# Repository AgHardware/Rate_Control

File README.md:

### [Nano RC12-2](Nano/RC12-2)
- uses a Nano (with ENC28J60 Ethernet shield) & an on-board mounted Cytron for rate control
	- either (1) [MD13S](https://www.cytron.io/p-13amp-6v-30v-dc-motor-driver) for single rate control
 	- or (1) [MD10C](https://www.cytron.io/c-motor-and-motor-driver/c-motor-driver/p-10amp-5v-30v-dc-motor-driver) for single rate control
- self assembled through-hole board, least expensive
- controls one rate
- can be connected to a relay module with another small pcb
- [OSHPARK](https://oshpark.com/shared_projects/UU8e90h9)

#
### [Teensy 4.1 RC11](Teensy/RC11_PCB)
- uses a Teensy & an on-board mounted Cytron for rate control
	- either (1) [MD13S](https://www.cytron.io/p-13amp-6v-30v-dc-motor-driver) for single rate control
 	- or (1) [MDD10A](https://www.cytron.io/p-10amp-5v-30v-dc-motor-driver-2-channels) for dual rate control
- small components are surface mount parts
- Teensy Ethernet or ESP8266 (ESP-12F) Wifi
- can control two rates and eight sections
	- 8 relays (SPST 12V output)
	- (2) 5V analog (pressure) inputs
	- (2) optically isolated digital (rate/pulse) inputs (5V)
- 5V Serial TTL header
- 3.3V I2C headers
	- supports optional external RelayDriver5 I2C board

#
### [ESP32 RC15](ESP32/RC15)
- uses an ESP32 (optional W5500 Ethernet Module)
- mostly surface mount parts
- can control two rates and 7-14 sections
	- (2) DRV8870 motor drivers with reversible outputs for rates
	- (7) DRV8870 motor drivers for either 7 reversible (motorized ball valve) outputs or 14 single ended (high or low) section outputs
- (4) 5V analog inputs (or 2 differential inputs)
- (2) optically isolated digital (rate/pulse) inputs, up to 12V
- RS485 chip & header
- 3.3V I2C header
	- supports optional external RelayDriver5 I2C board

#
### [RelayDriver5](RelayDriver5)
- PCA9535 based I2C IO expander
- designed to plug into 8 or 16 channel relay board with Qwiic cable

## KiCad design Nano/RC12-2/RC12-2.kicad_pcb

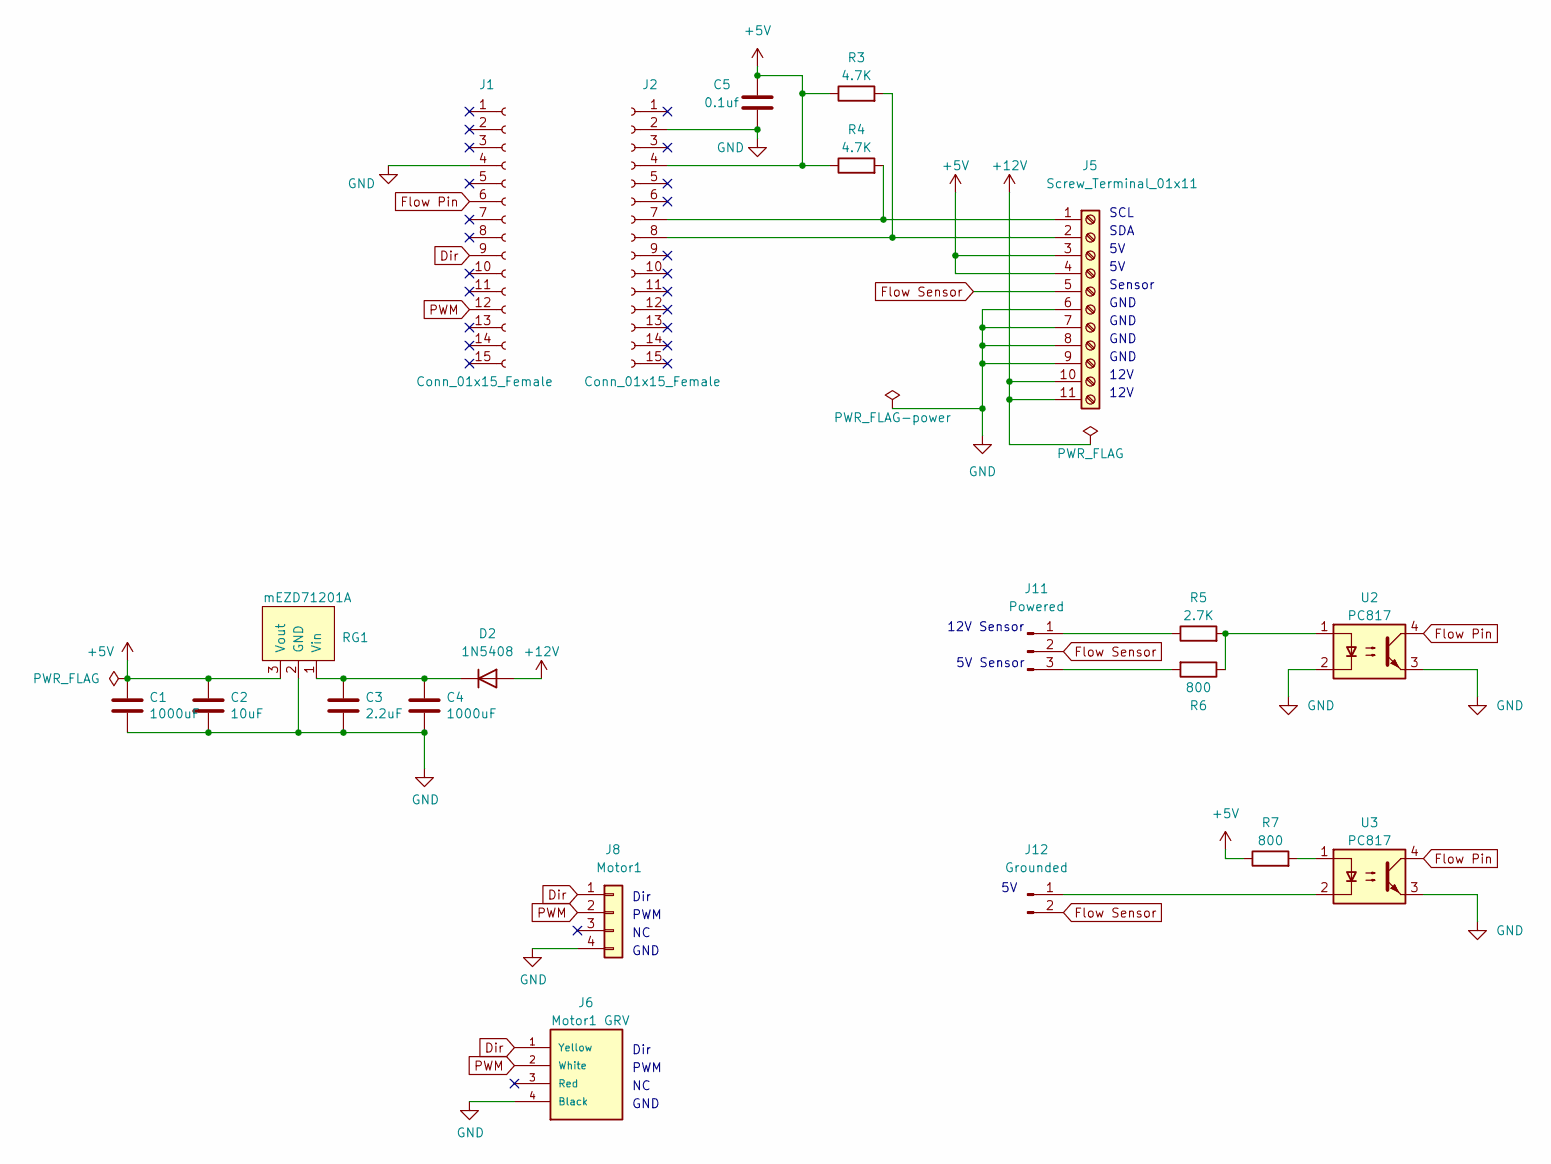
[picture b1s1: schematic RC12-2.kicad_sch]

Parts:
C1, C4: 1000uF; CP_Radial_D10.0mm_P5.00mm
C2: 10uF; C_Disc_D5.0mm_W2.5mm_P2.50mm
C3: 2.2uF; C_Disc_D5.0mm_W2.5mm_P2.50mm
C5: 0.1uf; C_Disc_D5.0mm_W2.5mm_P2.50mm
D2: 1N5408
J1, J2: Conn_01x15_Female; PinSocket_1x15_P2.54mm_Vertical
J5: Screw_Terminal_01x11; TerminalBlock_Phoenix_MKDS-1,5-11_1x11_P5.00mm_Horizontal
J6: Motor1 GRV; Grove
J8: Motor1; Molex_KK-254_AE-6410-04A_1x04_P2.54mm_Vertical
J11: Powered; PinHeader_1x03_P2.54mm_Vertical
J12: Grounded; PinHeader_1x02_P2.54mm_Vertical
R3, R4: 4.7K; R_Axial_DIN0207_L6.3mm_D2.5mm_P10.16mm_Horizontal
R5: 2.7K; R_Axial_DIN0207_L6.3mm_D2.5mm_P10.16mm_Horizontal
R6, R7: 800; R_Axial_DIN0207_L6.3mm_D2.5mm_P10.16mm_Horizontal
RG1: mEZD71201A
U2, U3: PC817

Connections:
+5V: C1.1, C2.1, C5.2, J2.4, J5.3, J5.4, R3.1, R4.1, R7.1, RG1.3 (Vout)
+12V: D2.2 (A), J5.10, J5.11
Dir: J1.9, J6.1 (Yellow), J8.1
Flow Pin: J1.6, U2.4, U3.4
Flow Sensor: J5.5, J11.2, J12.2
GND: C1.2, C2.2, C3.2, C4.2, C5.1, J1.4, J2.2, J5.6, J5.7, J5.8, J5.9, J6.4 (Black), J8.4, RG1.2 (GND), U2.2, U2.3, U3.3
unnamed: C3.1, C4.1, D2.1 (K), RG1.1 (Vin)
unnamed: J2.7, J5.1, R4.2
unnamed: J2.8, J5.2, R3.2
unnamed: J11.1, R5.1
unnamed: J11.3, R6.2
unnamed: J12.1, U3.2
unnamed: R5.2, R6.1, U2.1
unnamed: R7.2, U3.1
PWM: J1.12, J6.2 (White), J8.2

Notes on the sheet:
SCL
GND
SDA
5V Sensor
Dir
12V
12V Sensor
PWM
Sensor

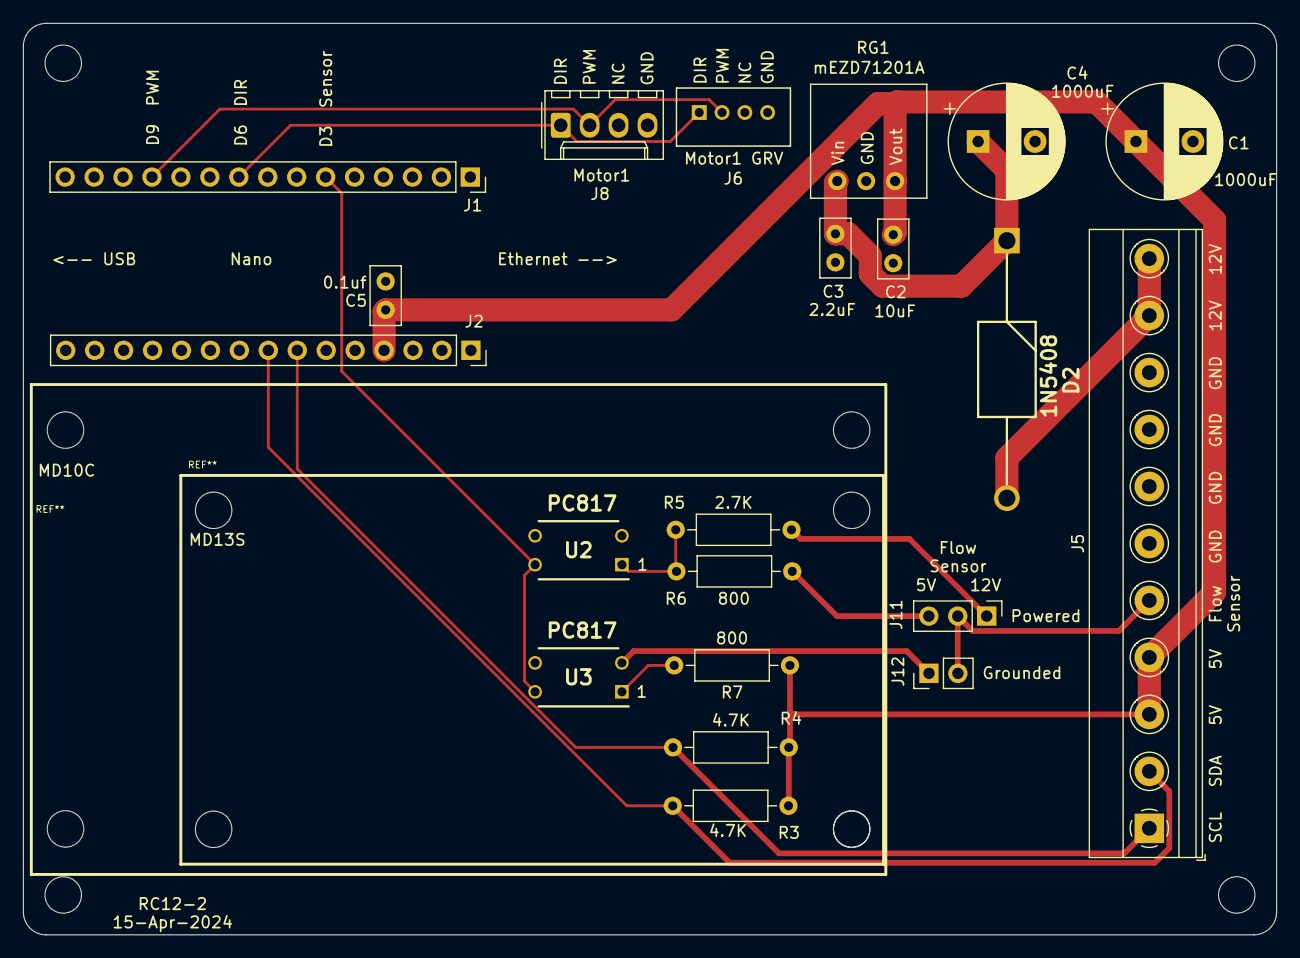
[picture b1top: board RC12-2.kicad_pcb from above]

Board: 2 copper layers, 110.0 x 80.0 mm, 25 parts (0 on the bottom side), 15 nets.

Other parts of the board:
 : MountingHole_3.2mm_M3
 #2,  #3,  #4: MountingHole_3.2mm_M3

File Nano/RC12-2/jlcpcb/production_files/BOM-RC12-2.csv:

Comment,Designator,Footprint,LCSC
2.7K,"R5,R6,R7",R_Axial_DIN0207_L6.3mm_D2.5mm_P10.16mm_Horizontal,C119333
4.7K,"R3,R4",R_Axial_DIN0207_L6.3mm_D2.5mm_P10.16mm_Horizontal,C119339
10uF,C2,C_Disc_D5.0mm_W2.5mm_P2.50mm,C2761733
Screw_Terminal_01x11,J5,"TerminalBlock_Phoenix_MKDS-1,5-11_1x11_P5.00mm_Horizontal",C2802625
Conn_01x15_Female,"J1,J2",PinSocket_1x15_P2.54mm_Vertical,C2932676
PC817,"U2,U3",PC817,C390734
Motor1 GRV,J6,Grove,C403774
Grounded,J12,PinHeader_1x02_P2.54mm_Vertical,C492401
Powered,J11,PinHeader_1x03_P2.54mm_Vertical,C49257
1000uF,"C1,C4",CP_Radial_D10.0mm_P5.00mm,C503217
2.2uF,C3,C_Disc_D5.0mm_W2.5mm_P2.50mm,C5181476
0.1uf,C5,C_Disc_D5.0mm_W2.5mm_P2.50mm,C5632430
1N5408,D2,1N5408,C698639
Motor1,J8,Molex_KK-254_AE-6410-04A_1x04_P2.54mm_Vertical,C86504
mEZD71201A,RG1,mEZD71201A,

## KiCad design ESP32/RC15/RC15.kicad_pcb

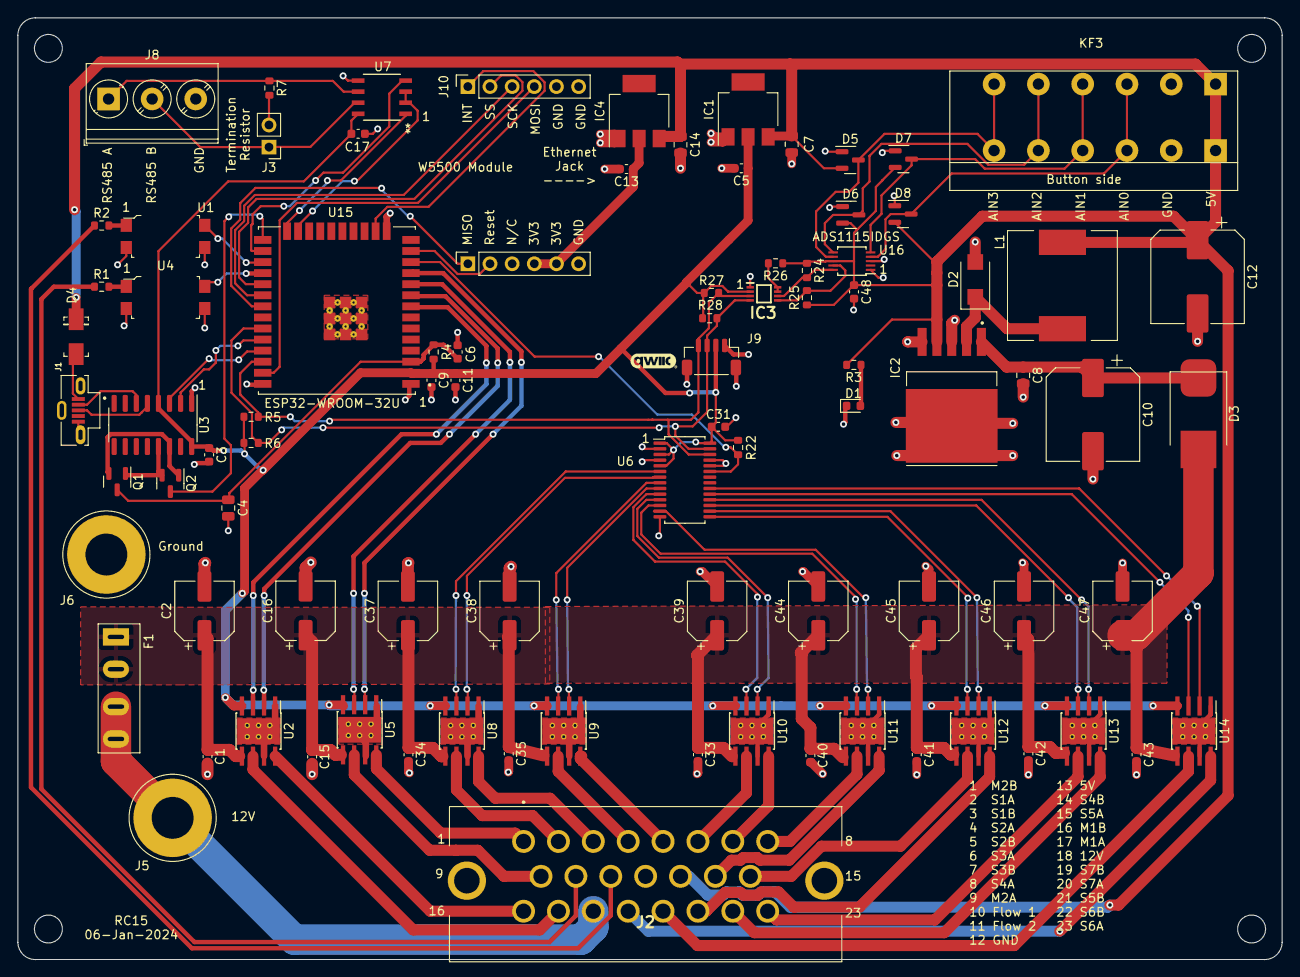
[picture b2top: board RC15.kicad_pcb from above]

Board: 2 copper layers, 145.0 x 108.0 mm, 92 parts (0 on the bottom side), 82 nets.

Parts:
 : MountingHole_3.2mm_M3
 #2,  #3,  #4: MountingHole_3.2mm_M3
C1, C3, C6, C9, C15, C17, C31, C33, C34, C35, C40, C41, C42, C43, C48: 0.1uF; C_0603_1608Metric
C2, C16, C37, C38, C39, C44, C45, C46, C47: 47uF; CP_Elec_6.3x5.4
C4, C8: 1uF; C_0805_2012Metric
C5, C11, C13: 22uF; C_0603_1608Metric
C7, C14: 10uF; C_0805_2012Metric
C10: 470uF; CP_Elec_10x10.5
C12: 330uF; CP_Elec_10x10.5
D1: LED; LED_0603_1608Metric
D2: SS36; SMA(DO-214AC)
D3: S10MC; D_SMC_larger_pads
D4: M7 - C95872; DO-214AC
D5, D6, D7, D8: BAV99; SOT-23
F1: C492610; Fuse_Holder_C492610
IC1, IC4: AZ1117; SOT-223
IC2: XL2596; TO263-5L
IC3: PCA9306DCUR
J1: 105133-0011; MOLEX_105133-0011
J2: 776087-1-776087-1; 7760871
J3: Conn_01x02_Pin; PinHeader_1x02_P2.54mm_Vertical
J5: 12V; PowerPin
J6: Ground; PowerPin
J7, J10: Conn_01x06_Socket; PinSocket_1x06_P2.54mm_Vertical
J8: Screw_Terminal_01x03; TerminalBlock_Phoenix_PT-1,5-3-5.0-H_1x03_P5.00mm_Horizontal
J9: I2C; Qwic_vertical
KF3: KF142V-5.0-6P; KF142V-5.08-6P
L1: SMDRI127-330MT; TMPA1265SP-101MN-D
Q1, Q2: BSS138; SOT-23
R1, R2: 2.7K; R_0603_1608Metric
R3: 500; R_0603_1608Metric
R4, R22: 10K; R_0603_1608Metric
R5, R6: 2.2K; R_0603_1608Metric
R7: 120; R_0603_1608Metric
R24, R25: 341; R_0603_1608Metric
R26: 200K; R_0603_1608Metric
R27, R28: 217; R_0603_1608Metric
U1, U4: PC817 chip; SMD-4_4.6x7.62mm_P2.54mm
U2, U5, U8, U9, U10, U11, U12, U13, U14: DRV8870DDA; Texas_HTSOP-8-1EP_3.9x4.9mm_P1.27mm_EP2.95x4.9mm_Mask2.4x3.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
U3: CH340C; SOIC-16_3.9x9.9mm_P1.27mm
U6: PCA9685PW; TSSOP-28_4.4x9.7mm_P0.65mm
U7: C9943; 21-0041B_8_MXM
U15: ESP32-WROOM-32U; XCVR_ESP32-WROOM-32U
U16: ADS1115IDGS; TSSOP-10_3x3mm_P0.5mm

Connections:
+3.3V: C3.1, C5.1, C9.1, C11.1, C17.1, C31.1, IC1.2 (OUTPUT), IC3.2 (VREF1), J9.2, R4.1, R5.1, R6.1, R22.1, R27.1, R28.1, U2.4 (VREF), U3.4 (V3), U3.16 (VCC), U5.4 (VREF), U6.1 (A0), U6.3 (A2), U6.5 (A4), U6.28 (VDD), U7.8 (VCC), U8.4 (VREF), U9.4 (VREF), U10.4 (VREF), U11.4 (VREF), U12.4 (VREF), U13.4 (VREF), U14.4 (VREF), U15.2 (3V3)
+5V: C7.1, C12.1, C14.1, C48.1, D4.1 (K), D5.2 (A), D6.2 (A), D7.2 (A), D8.2 (A), IC1.3 (INPUT), IC2.4 (Feedback), IC4.3 (INPUT), J2.13, KF3.1, L1.2, R3.2, R24.1, R25.1, R26.1, U16.8 (VDD)
+12V: C1.1, C2.1, C15.1, C16.1, C33.1, C34.1, C35.1, C37.1, C38.1, C39.1, C40.1, C41.1, C42.1, C43.1, C44.1, C45.1, C46.1, C47.1, D3.2 (A), F1.1, U2.5 (VM), U5.5 (VM), U8.5 (VM), U9.5 (VM), U10.5 (VM), U11.5 (VM), U12.5 (VM), U13.5 (VM), U14.5 (VM)
FlowPin1: U4.4, U15.28 (IO17)
FlowPin2: U1.4, U15.27 (IO16)
FlowSensor1: J2.10, R1.1
FlowSensor2: J2.11, R2.1
GND: C1.2, C2.2, C3.2, C4.2, C5.2, C6.2, C7.2, C8.2, C9.2, C10.2, C11.2, C12.2, C13.2, C14.2, C15.2, C16.2, C17.2, C31.2, C33.2, C34.2, C35.2, C37.2, C38.2, C39.2, C40.2, C41.2, C42.2, C43.2, C44.2, C45.2, C46.2, C47.2, C48.2, D1.1 (K), D2.2, D5.1 (K), D6.1 (K), D7.1 (K), D8.1 (K), IC1.1 (ADJ/GND), IC2.3 (GND), IC2.5 (On/Off), IC2.6 (GND_1), IC3.1 (GND), IC4.1 (ADJ/GND), J1.5 (GND), J1.S1 (SHIELD), J1.S2 (SHIELD), J1.S3 (SHIELD), J2.12, J6.1, J7.6, J8.3, J9.1, J9.MP (MountPin), J10.5, J10.6, KF3.2, U1.2, U1.3, U2.1 (GND), U2.7 (ISEN), U2.9 (GND), U3.1 (GND), U4.2, U4.3, U5.1 (GND), U5.7 (ISEN), U5.9 (GND), U6.2 (A1), U6.4 (A3), U6.14 (VSS), U6.24 (A5), U6.25 (EXTCLK), U7.5 (GND), U8.1 (GND), U8.7 (ISEN), U8.9 (GND), U9.1 (GND), U9.7 (ISEN), U9.9 (GND), U10.1 (GND), U10.7 (ISEN), U10.9 (GND), U11.1 (GND), U11.7 (ISEN), U11.9 (GND), U12.1 (GND), U12.7 (ISEN), U12.9 (GND), U13.1 (GND), U13.7 (ISEN), U13.9 (GND), U14.1 (GND), U14.7 (ISEN), U14.9 (GND), U15.1 (GND), U15.15 (GND), U15.38 (GND), U15.G.1 (GND), U15.G.2 (GND), U15.G.4 (GND), U15.G.5 (GND), U15.G.6 (GND), U15.G.7 (GND), U15.G.8 (GND), U15.G.9 (GND), U15.G.10 (GND), U15.G.11 (GND), U15.G.12 (GND), U15.G.13 (GND), U15.G.14 (GND), U15.G.15 (GND), U15.G.16 (GND), U15.G.17 (GND), U15.G.18 (GND), U15.G.19 (GND), U15.G.20 (GND), U15.G.21 (GND), U15.G.22 (GND), U16.1 (ADDR), U16.3 (GND)
INTn: J10.1, U15.16 (IO13)
M1A: J2.17, U2.6 (OUT1)
M1B: J2.16, U2.8 (OUT2)
M1_IN1: U2.3 (IN1), U15.8 (I032)
M1_IN2: U2.2 (IN2), U15.9 (I033)
M2A: J2.9, U5.6 (OUT1)
M2B: J2.1, U5.8 (OUT2)
M2_IN1: U5.3 (IN1), U15.10 (I025)
M2_IN2: U5.2 (IN2), U15.11 (I026)
MISO: J7.1, U15.31 (IO19)
MOSI: J10.4, U15.37 (IO23)
unnamed: D1.2 (A), R3.1
unnamed: C8.1, C10.1, D3.1 (K), IC2.1 (VIN)
unnamed: D4.2 (A), J1.1 (VBUS)
unnamed: D2.1, IC2.2 (Output), L1.1
unnamed: IC3.7 (VREF2), IC3.8 (EN), R26.2
unnamed: IC3.6 (SCL2), R24.2, U16.10 (SCL)
unnamed: IC3.5 (SDA2), R25.2, U16.9 (SDA)
unnamed: C13.1, IC4.2 (OUTPUT), J7.4, J7.5
unnamed: J1.3 (D+), U3.5 (UD+)
unnamed: J1.2 (D-), U3.6 (UD-)
unnamed: J3.1, J8.2, U7.7 (B)
unnamed: J3.2, R7.2
unnamed: F1.2, J2.18, J5.1
unnamed: J8.1, R7.1, U7.6 (A)
unnamed: Q1.1 (G), Q2.2 (S), U3.13 (~DTR)
unnamed: Q1.2 (S), Q2.1 (G), U3.14 (~RTS)
unnamed: Q2.3 (D), U15.25 (IO0)
unnamed: R1.2, U4.1
unnamed: R2.2, U1.1
unnamed: U6.6 (LED0), U8.3 (IN1)
unnamed: U6.7 (LED1), U8.2 (IN2)
unnamed: U6.8 (LED2), U9.3 (IN1)
unnamed: U6.9 (LED3), U9.2 (IN2)
unnamed: U6.10 (LED4), U10.3 (IN1)
unnamed: U6.11 (LED5), U10.2 (IN2)
unnamed: U6.12 (LED6), U11.3 (IN1)
unnamed: U6.13 (LED7), U11.2 (IN2)
unnamed: U6.15 (LED8), U12.3 (IN1)
unnamed: U6.16 (LED9), U12.2 (IN2)
unnamed: U6.17 (LED10), U13.3 (IN1)
unnamed: U6.18 (LED11), U13.2 (IN2)
unnamed: U6.19 (LED12), U14.3 (IN1)
unnamed: U6.20 (LED13), U14.2 (IN2)
unnamed: D8.3 (K), KF3.3, U16.4 (AIN0)
unnamed: D7.3 (K), KF3.4, U16.5 (AIN1)
unnamed: D6.3 (K), KF3.5, U16.6 (AIN2)
unnamed: D5.3 (K), KF3.6, U16.7 (AIN3)
OutputEnable: R22.2, U6.23 (~OE), U15.12 (IO27)
RS485_Enable: U7.2 (~RE), U7.3 (DE), U15.23 (IO15)
RX2: U7.1 (RO), U15.24 (IO2)
ResetNW: J7.2, U15.13 (IO14)
S1A: J2.2, U8.6 (OUT1)
S1B: J2.3, U8.8 (OUT2)
S2A: J2.4, U9.6 (OUT1)
S2B: J2.5, U9.8 (OUT2)
S3A: J2.6, U10.6 (OUT1)
S3B: J2.7, U10.8 (OUT2)
S4A: J2.8, U11.6 (OUT1)
S4B: J2.14, U11.8 (OUT2)
S5A: J2.15, U12.6 (OUT1)
S5B: J2.21, U12.8 (OUT2)
S6A: J2.23, U13.6 (OUT1)
S6B: J2.22, U13.8 (OUT2)
S7A: J2.20, U14.6 (OUT1)
S7B: J2.19, U14.8 (OUT2)
SCK: J10.3, U15.30 (IO18)
SCL: IC3.3 (SCL1), J9.4, R5.2, R27.2, U6.26 (SCL), U15.36 (IO22)
SDA: IC3.4 (SDA1), J9.3, R6.2, R28.2, U6.27 (SDA), U15.33 (IO21)
SS: J10.2, U15.29 (IO5)
TX2: U7.4 (DI), U15.26 (IO4)
uC_EN: C4.1, C6.1, Q1.3 (D), R4.2, U15.3 (EN)
uC_RX: U3.2 (TXD), U15.34 (RXD0)
uC_TX: U3.3 (RXD), U15.35 (TXD0)

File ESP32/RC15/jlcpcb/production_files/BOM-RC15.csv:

Comment,Designator,Footprint,LCSC
200K,R26,R_0603_1608Metric,C105574
2.7K,"R1,R2",R_0603_1608Metric,C13167
0.1uF,"C1,C15,C17,C3,C31,C33,C34,C35,C40,C41,C42,C43,C48,C6,C9",C_0603_1608Metric,C14663
10uF,"C14,C7",C_0805_2012Metric,C15850
I2C,J9,Qwic_vertical,C160390
S10MC,D3,D_SMC_larger_pads,C169472
120,R7,R_0603_1608Metric,C22787
500,R3,R_0603_1608Metric,C22808
341,"R24,R25",R_0603_1608Metric,C23138
BAV99,"D5,D6,D7,D8",SOT-23,C2500
BSS138,"Q1,Q2",SOT-23,C255592
10K,"R22,R4",R_0603_1608Metric,C25804
217,"R27,R28",R_0603_1608Metric,C25811
PCA9685PW,U6,TSSOP-28_4.4x9.7mm_P0.65mm,C2678753
1uF,"C4,C8",C_0805_2012Metric,C28323
47uF,"C16,C2,C37,C38,C39,C44,C45,C46,C47",CP_Elec_6.3x5.4,C2836440
SS36,D2,SMA(DO-214AC),C2903825
330uF,C12,CP_Elec_10x10.5,C3032175
470uF,C10,CP_Elec_10x10.5,C310845
PCA9306DCUR,IC3,PCA9306DCUR,C33196
ADS1115IDGS,U16,TSSOP-10_3x3mm_P0.5mm,C37593
776087-1-776087-1,J2,7760871,C378893
Conn_01x06_Socket,"J10,J7",PinSocket_1x06_P2.54mm_Vertical,C40877
2.2K,"R5,R6",R_0603_1608Metric,C4190
KF142V-5.0-6P,KF3,KF142V-5.08-6P,C475138
C492610,F1,Fuse_Holder_C492610,C492610
Screw_Terminal_01x03,J8,"TerminalBlock_Phoenix_PT-1,5-3-5.0-H_1x03_P5.00mm_Horizontal",C5188441
105133-0011,J1,MOLEX_105133-0011,C586226
22uF,"C11,C13,C5",C_0603_1608Metric,C59461
PC817 chip,"U1,U4",SMD-4_4.6x7.62mm_P2.54mm,C66405
ESP32-WROOM-32U,U15,XCVR_ESP32-WROOM-32U,C701344
XL2596,IC2,TO263-5L,C74190
Conn_01x02_Pin,J3,PinHeader_1x02_P2.54mm_Vertical,C7494857
LED,D1,LED_0603_1608Metric,C84263
CH340C,U3,SOIC-16_3.9x9.9mm_P1.27mm,C84681
DRV8870DDA,"U10,U11,U12,U13,U14,U2,U5,U8,U9",Texas_HTSOP-8-1EP_3.9x4.9mm_P1.27mm_EP2.95x4.9mm_Mask2.4x3.1mm_ThermalVias,C86590
AZ1117,"IC1,IC4",SOT-223,C92102
SMDRI127-330MT,L1,TMPA1265SP-101MN-D,C9400
M7 - C95872,D4,DO-214AC,C95872
C9943,U7,21-0041B_8_MXM,C9943
12V ,J5,PowerPin,
Ground,J6,PowerPin,

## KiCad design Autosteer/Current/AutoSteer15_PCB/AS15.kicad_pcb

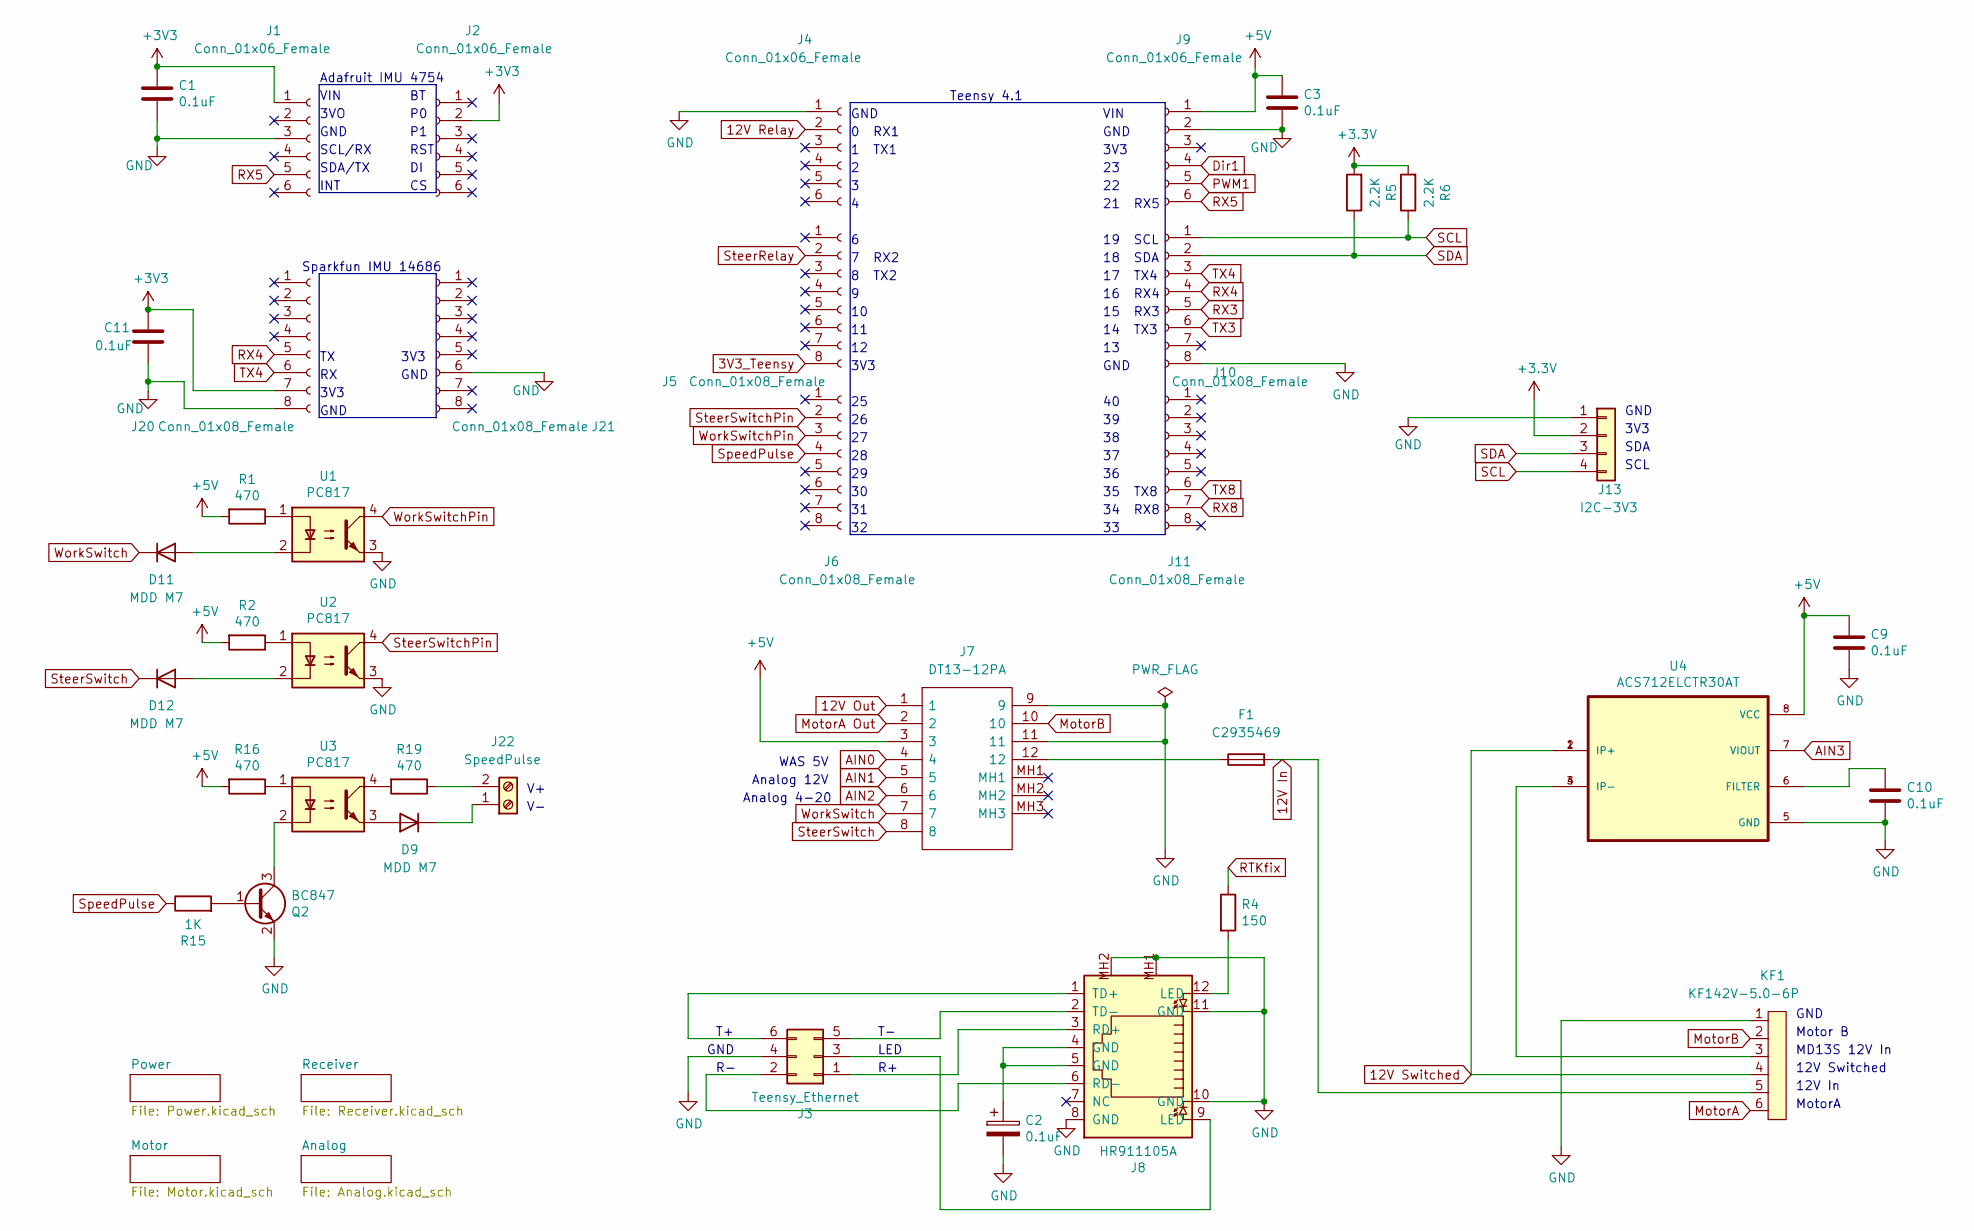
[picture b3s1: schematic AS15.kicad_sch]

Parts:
C1, C2, C3, C9, C10, C11: 0.1uF; C_0805_2012Metric
D9, D11, D12: MDD M7; D_SMA
F1: C2935469; Fuse_Holder_C2935469
J1, J2, J4, J9: Conn_01x06_Female; PinSocket_1x06_P2.54mm_Vertical
J3: Teensy_Ethernet; PinHeader_2x03_P2.00mm_Vertical
J5, J6, J10, J11, J20, J21: Conn_01x08_Female; PinSocket_1x08_P2.54mm_Vertical
J7: DT13-12PA; DT1312PA; Manufacturer_Part_Number DT13-12PA; Mouser Part Number 571-DT13-12PA
J8: HR911105A
J13: I2C-3V3; Qwic_vertical
J22: SpeedPulse; TerminalBlock_Phoenix_PT-1,5-2-5.0-H_1x02_P5.00mm_Horizontal
KF1: KF142V-5.0-6P; KF142V-5.08-6P
Q2: BC847; SOT-23
R1, R2, R16, R19: 470; R_0603_1608Metric
R4: 150; R_0603_1608Metric
R5, R6: 2.2K; R_0603_1608Metric
R15: 1K; R_0603_1608Metric
U1, U2, U3: PC817; SOIC254P960X420-4N
U4: ACS712ELCTR30AT; SOIC127P600X175-8N; PARTREV 1.0

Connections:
3V3_Teensy: J5.8; also elsewhere on the board
12V In: F1.2, KF1.5; also elsewhere on the board
12V Out: J7.1; also elsewhere on the board
12V Relay: J4.2; also elsewhere on the board
12V Switched: KF1.4, U4.1 (IP+), U4.2 (IP+); also elsewhere on the board
+5V: C3.1, C9.1, J7.3, J9.1, R1.2, R2.2, R16.2, U4.8 (VCC); also elsewhere on the board
AIN0: J7.4; also elsewhere on the board
AIN1: J7.5; also elsewhere on the board
AIN2: J7.6; also elsewhere on the board
AIN3: U4.7 (VIOUT); also elsewhere on the board
Dir1: J9.4; also elsewhere on the board
GND: C1.2, C2.2, C3.2, C9.2, C10.2, C11.2, J1.3, J3.4, J4.1, J7.9, J7.11, J8.8 (GND), J8.10 (GND), J8.11 (GND), J8.MH1, J8.MH2, J9.2, J10.8, J13.1, J20.8, J21.6, KF1.1, Q2.2 (E), U1.3, U2.3, U4.5 (GND); also elsewhere on the board
MotorA: KF1.6; also elsewhere on the board
MotorA Out: J7.2; also elsewhere on the board
MotorB: J7.10, KF1.2
unnamed: C2.1, J8.4 (GND), J8.5 (GND)
unnamed: C10.1, U4.6 (FILTER)
unnamed: D9.1 (K), J22.1
unnamed: D9.2 (A), U3.3
unnamed: F1.1, J7.12
unnamed: J3.1, J8.3 (RD+)
unnamed: J3.2, J8.6 (RD-)
unnamed: J3.3, J8.9 (LED)
unnamed: J3.5, J8.2 (TD-)
unnamed: J3.6, J8.1 (TD+)
unnamed: J8.12 (LED), R4.2
unnamed: J22.2, R19.1
unnamed: KF1.3, U4.3 (IP-), U4.4 (IP-)
unnamed: Q2.1 (B), R15.2
unnamed: Q2.3 (C), U3.2
unnamed: R1.1, U1.1
unnamed: R2.1, U2.1
unnamed: R16.1, U3.1
unnamed: R19.2, U3.4
unnamed: D11.2 (A), U1.2
unnamed: D12.2 (A), U2.2
PWM1: J9.5; also elsewhere on the board
RTKfix: R4.1; also elsewhere on the board
RX3: J10.5; also elsewhere on the board
RX4: J10.4, J20.5
RX5: J1.5, J9.6
RX8: J11.7; also elsewhere on the board
SCL: J10.1, J13.4, R6.1; also elsewhere on the board
SDA: J10.2, J13.3, R5.1; also elsewhere on the board
SpeedPulse: J6.4, R15.1
SteerRelay: J5.2; also elsewhere on the board
SteerSwitch: D12.1 (K), J7.8
SteerSwitchPin: J6.2, U2.4
TX3: J10.6; also elsewhere on the board
TX4: J10.3, J20.6
TX8: J11.6; also elsewhere on the board
WorkSwitch: D11.1 (K), J7.7
WorkSwitchPin: J6.3, U1.4

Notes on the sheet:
3V3
SDA
GND
Analog 4-20
7 RX2
19 SCL
Teensy 4.1
Motor B
LED
8 TX2
Analog 12V
35 TX8
16 RX4
SCL/RX
WAS 5V
14 TX3
VIN
17 TX4
RST
3VO
12V In
MotorA
MD13S 12V In
34 RX8
Sparkfun IMU 14686
12V Switched
1 TX1
18 SDA
INT
0 RX1
SDA/TX
21 RX5
SCL
15 RX3
Adafruit IMU 4754

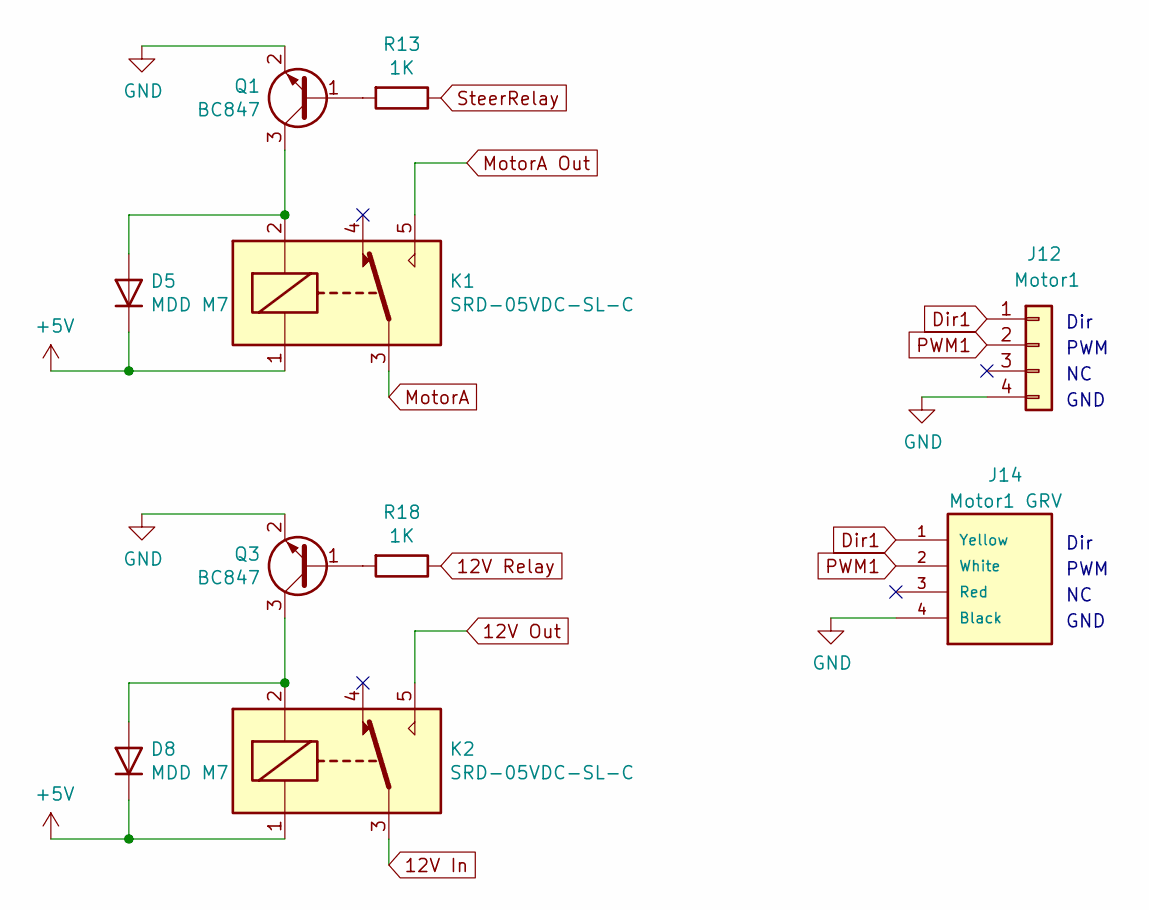
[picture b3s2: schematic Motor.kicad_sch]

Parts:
D5, D8: MDD M7; D_SMA
J12: Motor1; Molex_KK-254_AE-6410-04A_1x04_P2.54mm_Vertical
J14: Motor1 GRV; Grove
K1, K2: SRD-05VDC-SL-C; Songle_SRD-05VDC-SL-C
Q1, Q3: BC847; SOT-23
R13, R18: 1K; R_0603_1608Metric

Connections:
12V In: K2.3; also elsewhere on the board
12V Out: K2.5; also elsewhere on the board
12V Relay: R18.1; also elsewhere on the board
+5V: D5.1 (K), D8.1 (K), K1.1, K2.1; also elsewhere on the board
Dir1: J12.1, J14.1 (Yellow); also elsewhere on the board
GND: J12.4, J14.4 (Black), Q1.2 (E), Q3.2 (E); also elsewhere on the board
MotorA: K1.3; also elsewhere on the board
MotorA Out: K1.5; also elsewhere on the board
unnamed: D5.2 (A), K1.2, Q1.3 (C)
unnamed: D8.2 (A), K2.2, Q3.3 (C)
unnamed: Q1.1 (B), R13.2
unnamed: Q3.1 (B), R18.2
PWM1: J12.2, J14.2 (White); also elsewhere on the board
SteerRelay: R13.1; also elsewhere on the board

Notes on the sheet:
GND
Dir
PWM

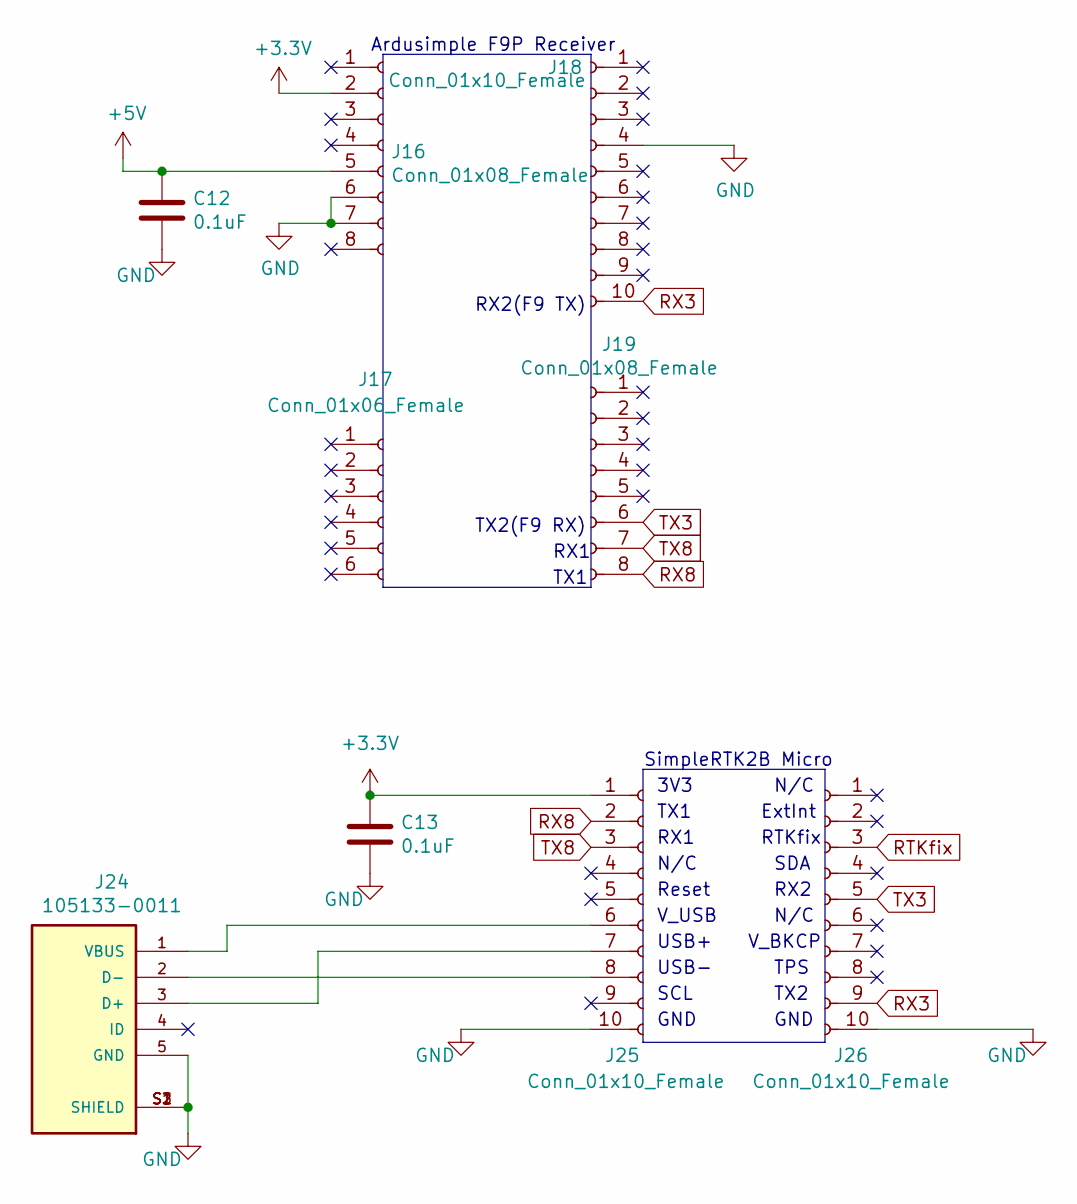
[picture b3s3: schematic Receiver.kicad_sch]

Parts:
C12, C13: 0.1uF; C_0805_2012Metric
J16, J19: Conn_01x08_Female; PinSocket_1x08_P2.54mm_Vertical
J17: Conn_01x06_Female; PinSocket_1x06_P2.54mm_Vertical
J18: Conn_01x10_Female; PinSocket_1x10_P2.54mm_Vertical
J24: 105133-0011; MOLEX_105133-0011; PARTREV C
J25, J26: Conn_01x10_Female; PinSocket_1x10_P2.00mm_Vertical

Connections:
+5V: C12.1, J16.5; also elsewhere on the board
GND: C12.2, C13.2, J16.6, J16.7, J18.4, J24.5 (GND), J24.S1 (SHIELD), J24.S2 (SHIELD), J24.S3 (SHIELD), J25.10, J26.10; also elsewhere on the board
unnamed: J24.1 (VBUS), J25.6
unnamed: J24.2 (D-), J25.8
unnamed: J24.3 (D+), J25.7
RTKfix: J26.3; also elsewhere on the board
RX3: J18.10, J26.9; also elsewhere on the board
RX8: J19.8, J25.2; also elsewhere on the board
TX3: J19.6, J26.5; also elsewhere on the board
TX8: J19.7, J25.3; also elsewhere on the board

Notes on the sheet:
RX1
3V3
TX1
SCL
RX2(F9 TX)
GND
N/C
USB-
TPS
SDA
TX2
V_USB
V_BKCP
RX2
ExtInt
Reset
Ardusimple F9P Receiver
SimpleRTK2B Micro
RTKfix
TX2(F9 RX)
USB+

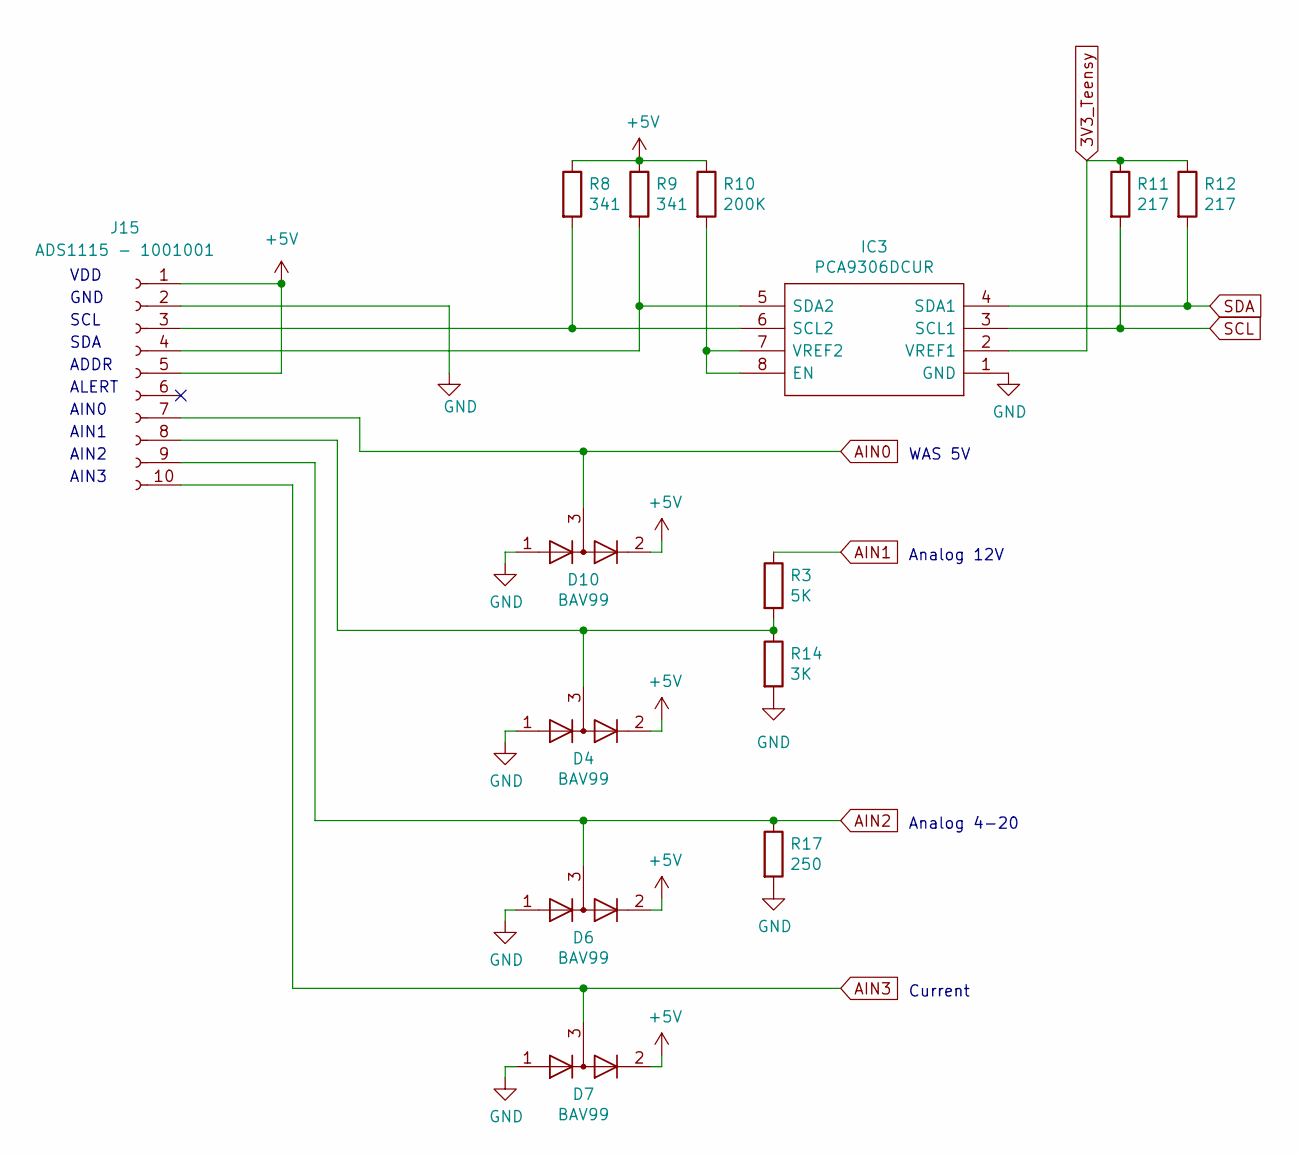
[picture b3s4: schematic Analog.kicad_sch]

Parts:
D4, D6, D7, D10: BAV99; SOT-23
IC3: PCA9306DCUR; Mouser Part Number 595-PCA9306DCUR
J15: ADS1115 - 1001001; PinSocket_1x10_P2.54mm_Vertical
R3: 5K; R_0603_1608Metric
R8, R9: 341; R_0603_1608Metric
R10: 200K; R_0603_1608Metric
R11, R12: 217; R_0603_1608Metric
R14: 3K; R_0603_1608Metric
R17: 250; R_0603_1608Metric

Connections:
3V3_Teensy: IC3.2 (VREF1), R11.1, R12.1; also elsewhere on the board
+5V: D4.2 (A), D6.2 (A), D7.2 (A), D10.2 (A), J15.1, J15.5, R8.1, R9.1, R10.1; also elsewhere on the board
AIN0: D10.3 (K), J15.7; also elsewhere on the board
AIN1: R3.1; also elsewhere on the board
AIN2: D6.3 (K), J15.9, R17.1; also elsewhere on the board
AIN3: D7.3 (K), J15.10; also elsewhere on the board
GND: D4.1 (K), D6.1 (K), D7.1 (K), D10.1 (K), IC3.1 (GND), J15.2, R14.2, R17.2; also elsewhere on the board
unnamed: D4.3 (K), J15.8, R3.2, R14.1
unnamed: IC3.5 (SDA2), J15.4, R9.2
unnamed: IC3.6 (SCL2), J15.3, R8.2
unnamed: IC3.7 (VREF2), IC3.8 (EN), R10.2
SCL: IC3.3 (SCL1), R11.2; also elsewhere on the board
SDA: IC3.4 (SDA1), R12.2; also elsewhere on the board

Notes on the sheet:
AIN1
WAS 5V
ADDR
GND
Analog 4-20
AIN2
SCL
ALERT
VDD
SDA
AIN3
Current
Analog 12V
AIN0

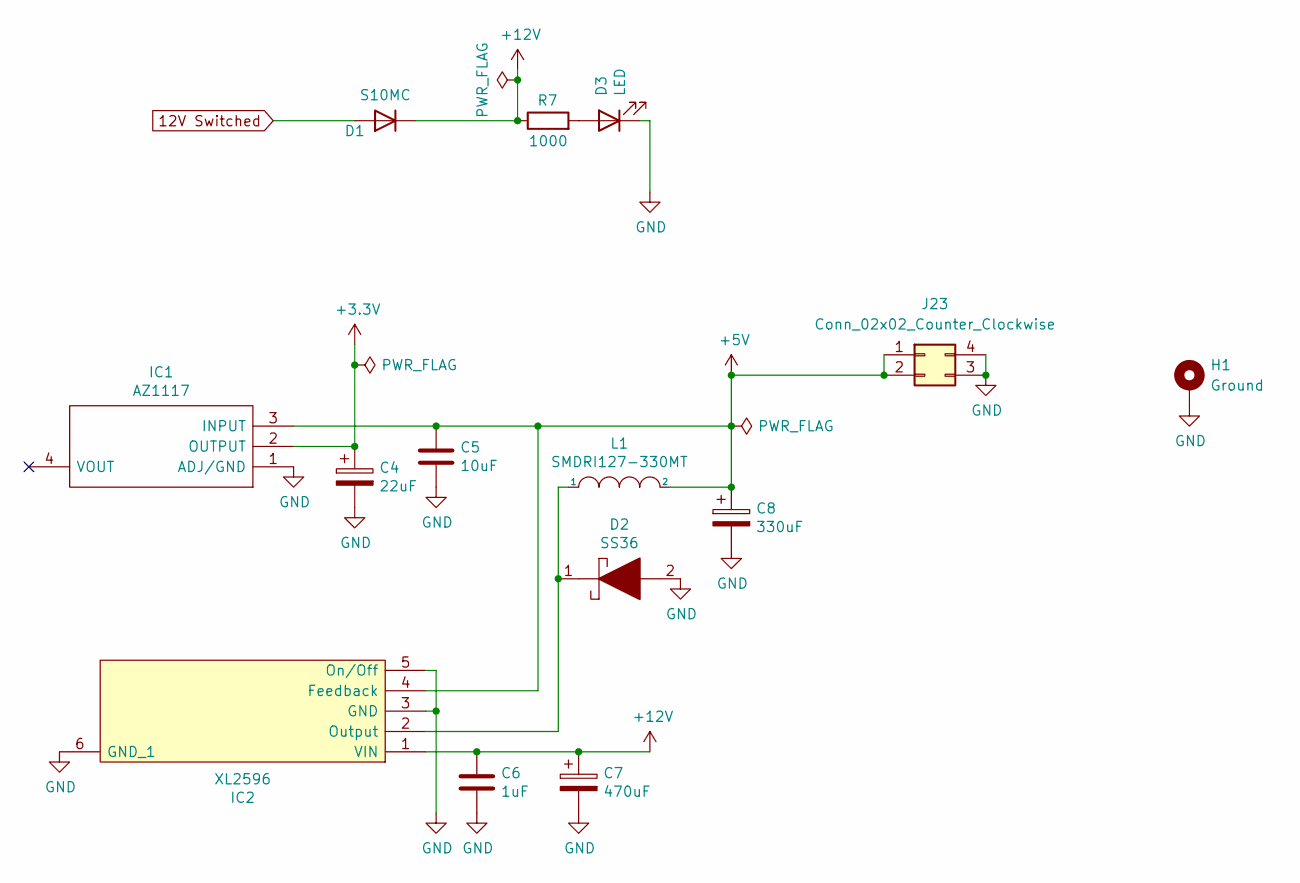
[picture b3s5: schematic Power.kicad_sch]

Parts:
C4: 22uF; C_0805_2012Metric
C5: 10uF; C_0805_2012Metric
C6: 1uF; C_0805_2012Metric
C7: 470uF; CP_Elec_10x10.5
C8: 330uF; CP_Elec_10x10.5
D1: S10MC; D_SMC_larger_pads
D2: SS36; SMA(DO-214AC)
D3: LED; LED_0805_2012Metric
H1: Ground; MountingHole_2.2mm_M2_DIN965_Pad
IC1: AZ1117; SOT-223
IC2: XL2596; TO263-5L
J23: Conn_02x02_Counter_Clockwise; PinSocket_2x02_P2.54mm_Vertical
L1: SMDRI127-330MT; TMPA1265SP-101MN-D
R7: 1000; R_0603_1608Metric

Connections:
12V Switched: D1.2 (A); also elsewhere on the board
+5V: C5.1, C8.1, IC1.3 (INPUT), IC2.4 (Feedback), J23.1, J23.2, L1.2; also elsewhere on the board
+12V: C6.1, C7.1, D1.1 (K), IC2.1 (VIN), R7.1
GND: C4.2, C5.2, C6.2, C7.2, C8.2, D2.2, D3.1 (K), H1.1, IC1.1 (ADJ/GND), IC2.3 (GND), IC2.5 (On/Off), IC2.6 (GND_1), J23.3, J23.4; also elsewhere on the board
unnamed: D2.1, IC2.2 (Output), L1.1
unnamed: D3.2 (A), R7.2

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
